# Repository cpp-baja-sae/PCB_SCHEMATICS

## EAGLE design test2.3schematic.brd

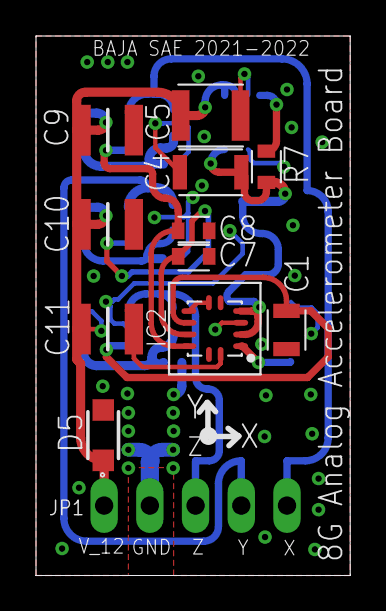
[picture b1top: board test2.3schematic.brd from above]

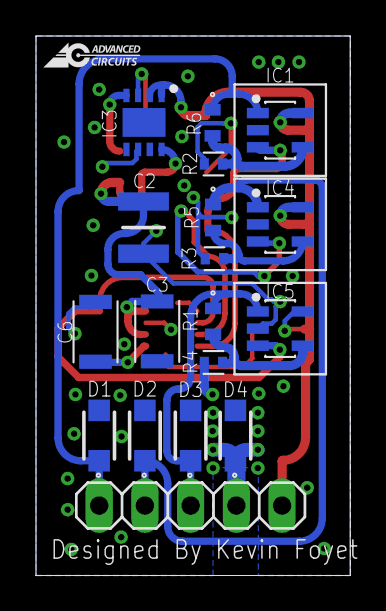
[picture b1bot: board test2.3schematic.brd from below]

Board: 2 copper layers, 17.5 x 30.0 mm, 29 parts (18 on the bottom side), 14 nets.

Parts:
C1: CGA4C2C0G1H822J060AA; CAPC2012X145N
C2: CGA6P3X7R1H475K250AD; CAPC3225X280N
C3, C6: CGA5L2C0G1H104J160AA; CAPC3216X180N
C4: CGA5L3X7R1H225K160AB; CAPC3317X190N
C5: CGA6M2X7R1H155K200AA; CAPC3225X220N
C7, C8: CGA3E2C0G1H332J080AA; CAPC1608X90N
C9, C10, C11: CNA6P1X7R1H475K250AE; CAPC3225X280N
D1, D2, D3, D4, D5: PTVS12VS1UR,115; SOD123W
IC1, IC4, IC5: NCS21911SN2T1G; SOT95P275X110-5N
IC2: FXLN8371QR1; QFN65P300X300X100-12N
IC3: MAX25210ATAB9_V+; SON65P300X300X80-9N
JP1: 1X05
R1, R5, R6: ERA-3ARB182V; ERA3A_(0603)
R2, R3, R4: ERA-2ARB2100X; RESC1005X40N
R7: ERJ-PB3B1002V; RESC1608X55N

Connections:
BYP: C6.1, IC2.1
GND: C1.2, C2.2, C3.2, C4.2, C5.2, C6.2, C7.2, C8.2, C9.2, C10.2, C11.2, D1.2, D2.2, D3.2, D4.1, D4.2, D5.2, IC1.2, IC2.3, IC2.5, IC2.6, IC2.7, IC2.11, IC2.12, IC3.3, IC3.6, IC3.7, IC3.9, IC4.2, IC5.2, JP1.2, R2.2, R3.2, R4.2
V_3.3V: C2.1, C3.1, C4.1, IC2.2, IC2.4, IC3.8, R7.1
V_12V: C5.1, C9.1, C10.1, C11.1, D5.1, IC1.5, IC3.1, IC3.2, IC4.5, IC5.5, JP1.1
V_RESET: IC3.4, R7.2
X_AXIS: C8.1, IC1.3, IC2.10
X_OUT: D1.1, IC1.1, JP1.5, R6.1
X_OUT_F: IC1.4, R2.1, R6.2
Y_AXIS: C7.1, IC2.9, IC4.3
Y_OUT: D2.1, IC4.1, JP1.4, R5.1
Y_OUT_F: IC4.4, R3.1, R5.2
Z_AXIS: C1.1, IC2.8, IC5.3
Z_OUT: D3.1, IC5.1, JP1.3, R1.1
Z_OUT_F: IC5.4, R1.2, R4.1

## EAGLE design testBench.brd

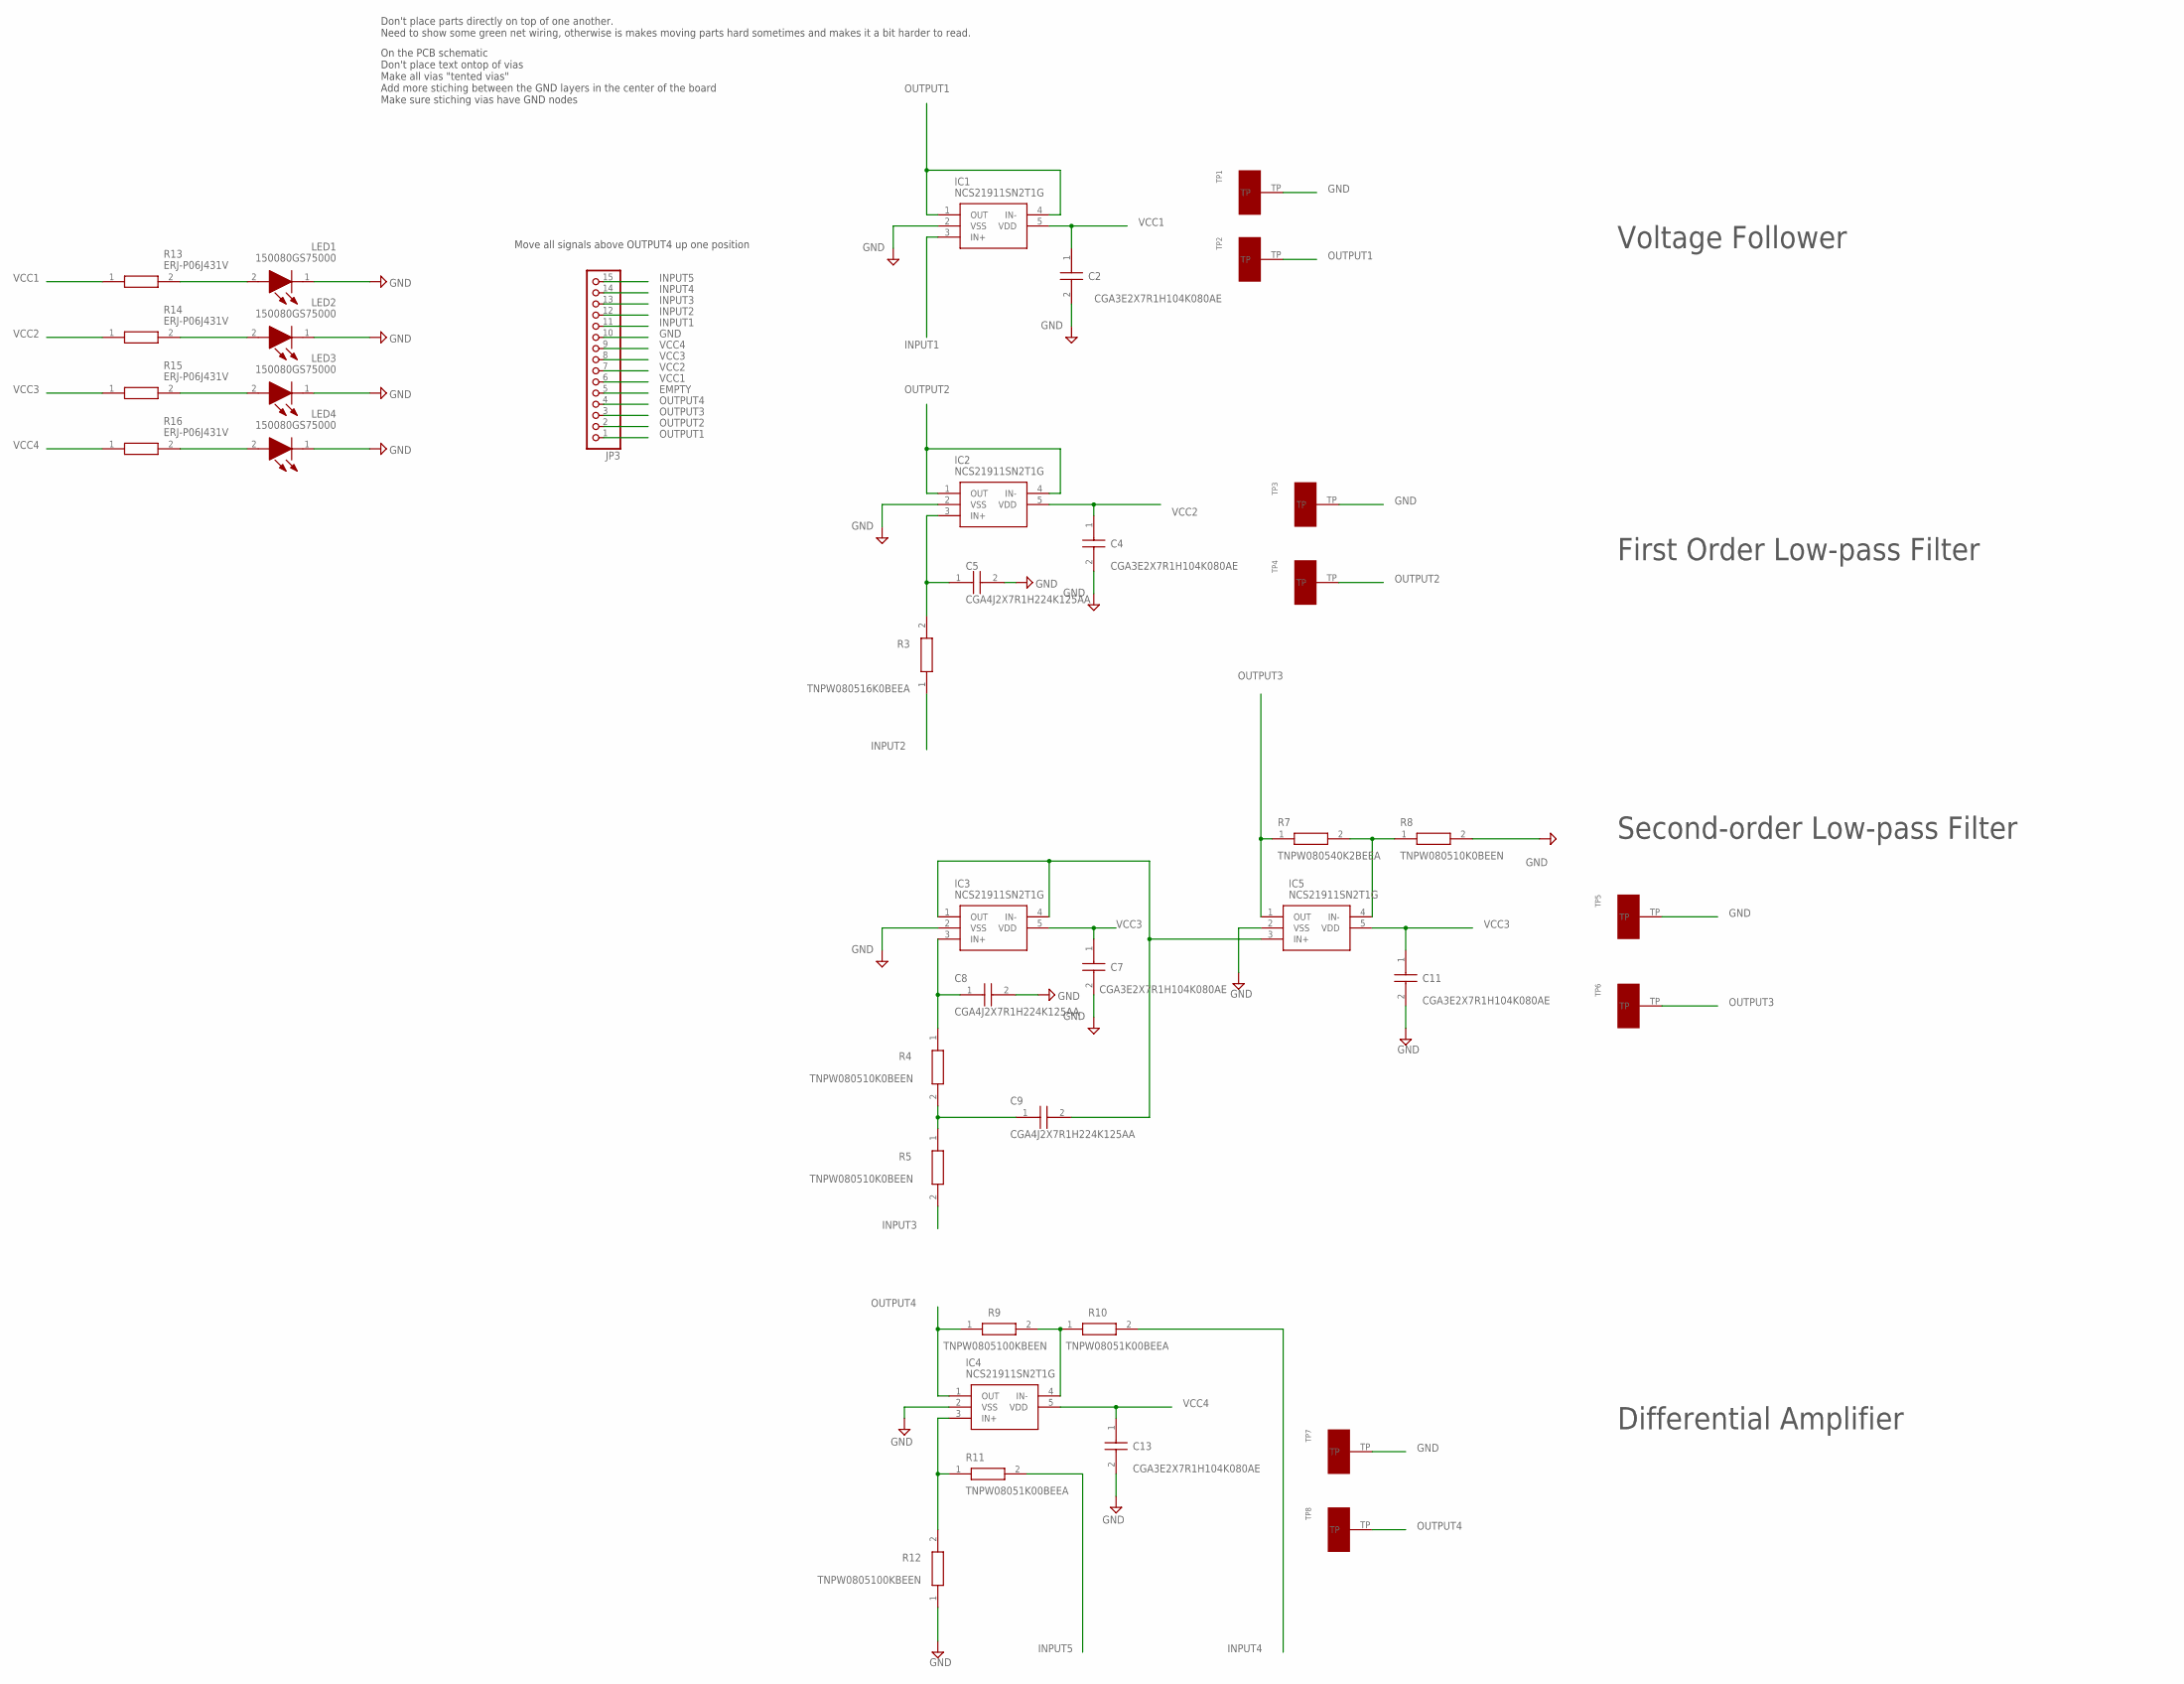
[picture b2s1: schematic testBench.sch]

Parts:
C2, C4, C7, C11, C13: CGA3E2X7R1H104K080AE; CAPC1608X90N
C5, C8, C9: CGA4J2X7R1H224K125AA; CAPC2012X145N
IC1, IC2, IC3, IC4, IC5: NCS21911SN2T1G; SOT95P275X110-5N
JP3: PINHD-1X15; 1X15
LED1, LED2, LED3, LED4: 150080GS75000; LEDM2012X80N
R3: TNPW080516K0BEEA; RESC2013X65N
R4, R5, R8: TNPW080510K0BEEN; RESC2013X65N
R7: TNPW080540K2BEEA; RESC2013X65N
R9, R12: TNPW0805100KBEEN; RESC2013X65N
R10, R11: TNPW08051K00BEEA; RESC2012X55N
R13, R14, R15, R16: ERJ-P06J431V; ERJP06_(0805)
TP1, TP2, TP3, TP4, TP5, TP6, TP7, TP8: S1751-46R; 1.85X3.45_MM

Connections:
EMPTY: JP3.5
GND: C2.2, C4.2, C5.2, C7.2, C8.2, C11.2, C13.2, IC1.2 (VSS), IC2.2 (VSS), IC3.2 (VSS), IC4.2 (VSS), IC5.2 (VSS), JP3.10, LED1.1 (K), LED2.1 (K), LED3.1 (K), LED4.1 (K), R8.2, R12.1, TP1.TP, TP3.TP, TP5.TP, TP7.TP
INPUT1: IC1.3 (IN+), JP3.11
INPUT2: JP3.12, R3.1
INPUT3: JP3.13, R5.2
INPUT4: JP3.14, R10.2
INPUT5: JP3.15, R11.2
unnamed: C8.1, IC3.3 (IN+), R4.1
unnamed: C9.1, R4.2, R5.1
unnamed: C9.2, IC3.1 (OUT), IC3.4 (IN-), IC5.3 (IN+)
unnamed: IC4.3 (IN+), R11.1, R12.2
unnamed: C5.1, IC2.3 (IN+), R3.2
unnamed: IC4.4 (IN-), R9.2, R10.1
unnamed: IC5.4 (IN-), R7.2, R8.1
unnamed: LED1.2 (A), R13.2
unnamed: LED2.2 (A), R14.2
unnamed: LED3.2 (A), R15.2
unnamed: LED4.2 (A), R16.2
OUTPUT1: IC1.1 (OUT), IC1.4 (IN-), JP3.1, TP2.TP
OUTPUT2: IC2.1 (OUT), IC2.4 (IN-), JP3.2, TP4.TP
OUTPUT3: IC5.1 (OUT), JP3.3, R7.1, TP6.TP
OUTPUT4: IC4.1 (OUT), JP3.4, R9.1, TP8.TP
VCC1: C2.1, IC1.5 (VDD), JP3.6, R13.1
VCC2: C4.1, IC2.5 (VDD), JP3.7, R14.1
VCC3: C7.1, C11.1, IC3.5 (VDD), IC5.5 (VDD), JP3.8, R15.1
VCC4: C13.1, IC4.5 (VDD), JP3.9, R16.1

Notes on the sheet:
Voltage Follower
First Order Low-pass Filter
Second-order Low-pass Filter
Differential Amplifier
Move all signals above OUTPUT4 up one position
Don't place parts directly on top of one another. Need to show some green net wiring, otherwise is makes moving parts hard sometimes and makes it a bit harder to read.
On the PCB schematic Don't place text ontop of vias Make all vias "tented vias" Add more stiching between the GND layers in the center of the board Make sure stiching vias have GND nodes

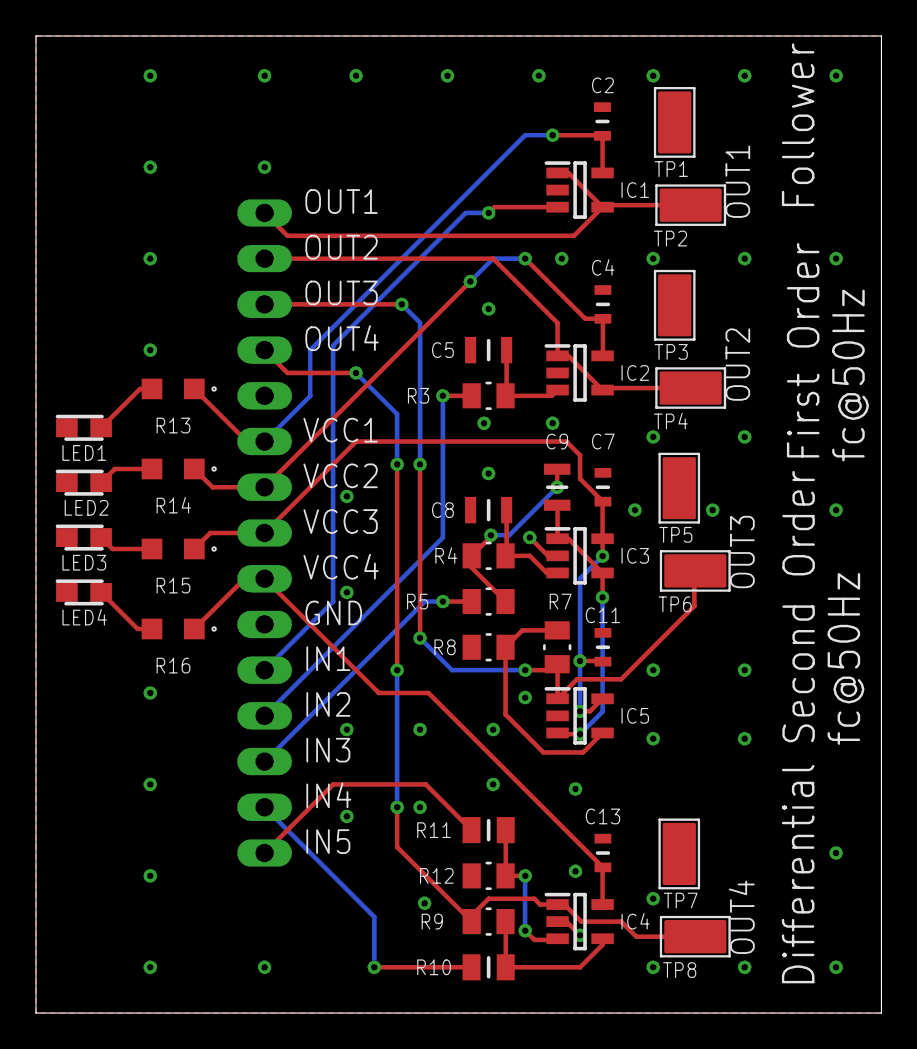
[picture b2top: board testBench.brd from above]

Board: 2 copper layers, 47.0 x 54.3 mm, 39 parts (1 on the bottom side), 25 nets.
